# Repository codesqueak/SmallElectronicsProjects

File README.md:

# Small Electronics Projects

A collection of small projects for the Nascom 1 & 2 that don't need their own project space

# Nascom 1 Clock

A replacement, and somewhat less noisy, clock circuit

# Nascom 2 Graphics Adaptor

Full Nascom 2 graphics on the Nascom 1

# Nascom 2 Screen Flash Eliminator

A gadget to reduce screen flash on N2 video

# Solar Garden Light

Uses one NiMH battery and a 2.5v solar panel

# Grove to Raspberry Pi Adaptor

A simple adaptor to allow a set of Grove connector devices to be attached the to 5v/GND/SCL/SDA pins on the RPi connector

# Grove to Raspberry Pi Adaptor (Mixed)

A simple adaptor to allow a set of Grove connector devices to be attached the to 5v/GND/SCL/SDA pins on the RPi connector

# A LIPO Based Garden Light

Use a protected battery !

# A Compact  LIPO Based Garden Light

Use a protected battery !

# Nascom 1 Keyboard Adaptor

Small adaptor to allow use of the N2 keyboard connector on an N1

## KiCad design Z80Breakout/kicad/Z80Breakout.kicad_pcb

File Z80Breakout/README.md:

# Z80 Breakout Board

A board to allow easy access to Z80 pins / use of a ZIF socket

## Parts:

1. 40 pin ZIF socket
2. 2 x 20 turned pin SIL strips (Pins to go into the socket on the target system)
3. 2 x 20 pin SIL strip (Pins for the scope / LA connections). Lot’s on eBay – used a lot with RPi’s etc – Usually a lot cheaper than the turned pin strips !

## Construction

1. Solder the turned pin strips in first. (On the bottom of the board)
2. Trim down with snips on the top as the ZIF socket will sit on top of this.
3. Solder the scope / LA pin strips on the top of the board
4. Trim any pins sticking out the bottom
5. Solder in the ZIF socket – Be careful, it’s a bit close to the SIL strips used to insert into the CPU socket
6. Add pins to the +5v and GND via’s if you want these
7. Test all pins to make sure you have not shorted any while soldering.

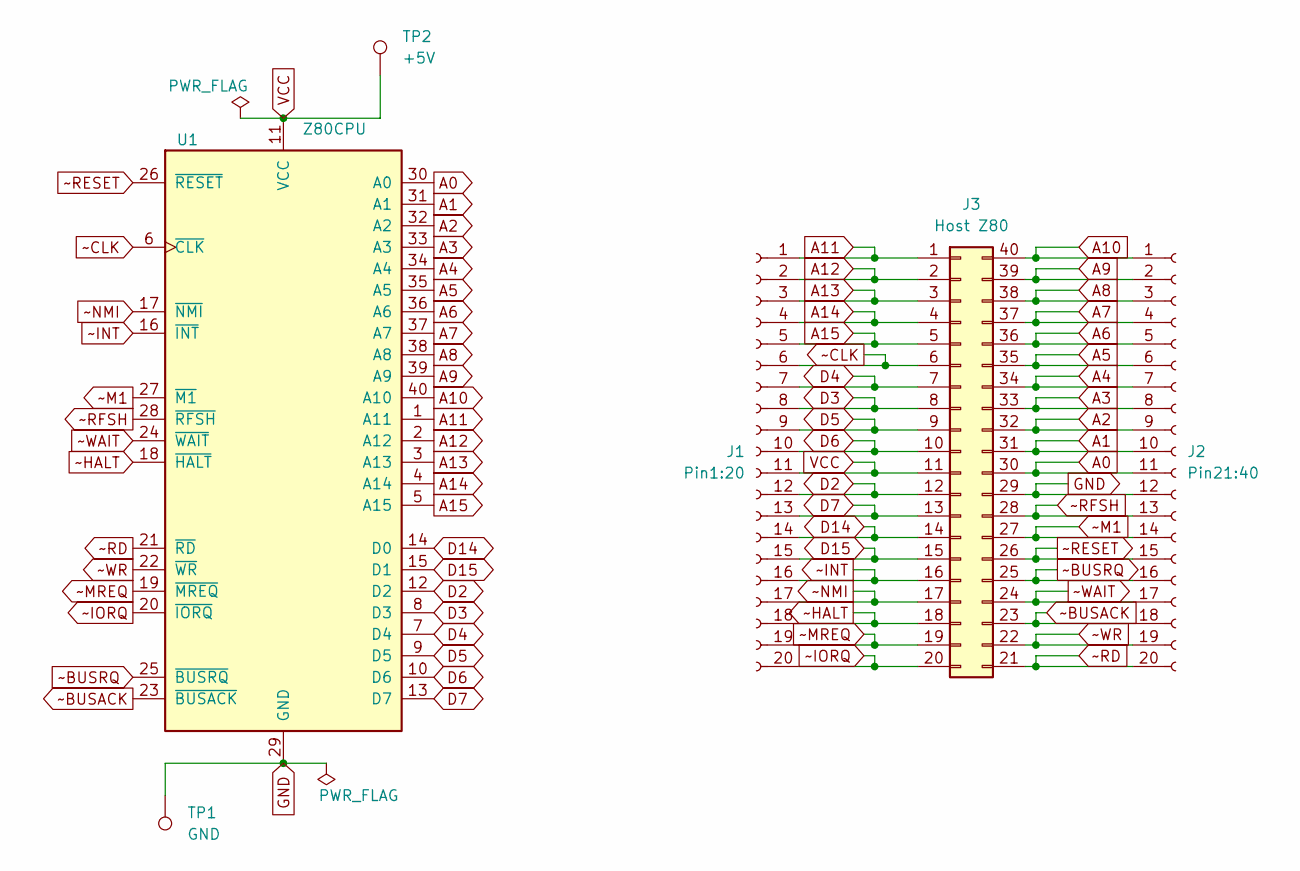
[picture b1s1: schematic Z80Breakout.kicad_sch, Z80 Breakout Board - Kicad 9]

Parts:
J1: Pin1:20; PinHeader_1x20_P2.54mm_Vertical
J2: Pin21:40; PinHeader_1x20_P2.54mm_Vertical
J3: Host Z80; DIP-40_W15.24mm
TP1: GND; TestPoint_THTPad_D2.0mm_Drill1.0mm
TP2: +5V; TestPoint_THTPad_D2.0mm_Drill1.0mm
U1: Z80CPU; DIP-40_W15.24mm_ZIF

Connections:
A0: J2.11, J3.30, U1.30 (A0)
A1: J2.10, J3.31, U1.31 (A1)
A2: J2.9, J3.32, U1.32 (A2)
A3: J2.8, J3.33, U1.33 (A3)
A4: J2.7, J3.34, U1.34 (A4)
A5: J2.6, J3.35, U1.35 (A5)
A6: J2.5, J3.36, U1.36 (A6)
A7: J2.4, J3.37, U1.37 (A7)
A8: J2.3, J3.38, U1.38 (A8)
A9: J2.2, J3.39, U1.39 (A9)
A10: J2.1, J3.40, U1.40 (A10)
A11: J1.1, J3.1, U1.1 (A11)
A12: J1.2, J3.2, U1.2 (A12)
A13: J1.3, J3.3, U1.3 (A13)
A14: J1.4, J3.4, U1.4 (A14)
A15: J1.5, J3.5, U1.5 (A15)
D2: J1.12, J3.12, U1.12 (D2)
D3: J1.8, J3.8, U1.8 (D3)
D4: J1.7, J3.7, U1.7 (D4)
D5: J1.9, J3.9, U1.9 (D5)
D6: J1.10, J3.10, U1.10 (D6)
D7: J1.13, J3.13, U1.13 (D7)
D14: J1.14, J3.14, U1.14 (D0)
D15: J1.15, J3.15, U1.15 (D1)
GND: J2.12, J3.29, TP1.1, U1.29 (GND)
VCC: J1.11, J3.11, TP2.1, U1.11 (VCC)
~BUSACK: J2.18, J3.23, U1.23 (~BUSACK)
~BUSRQ: J2.16, J3.25, U1.25 (~BUSRQ)
~CLK: J1.6, J3.6, U1.6 (~CLK)
~HALT: J1.18, J3.18, U1.18 (~HALT)
~INT: J1.16, J3.16, U1.16 (~INT)
~IORQ: J1.20, J3.20, U1.20 (~IORQ)
~M1: J2.14, J3.27, U1.27 (~M1)
~MREQ: J1.19, J3.19, U1.19 (~MREQ)
~NMI: J1.17, J3.17, U1.17 (~NMI)
~RD: J2.20, J3.21, U1.21 (~RD)
~RESET: J2.15, J3.26, U1.26 (~RESET)
~RFSH: J2.13, J3.28, U1.28 (~RFSH)
~WAIT: J2.17, J3.24, U1.24 (~WAIT)
~WR: J2.19, J3.22, U1.22 (~WR)

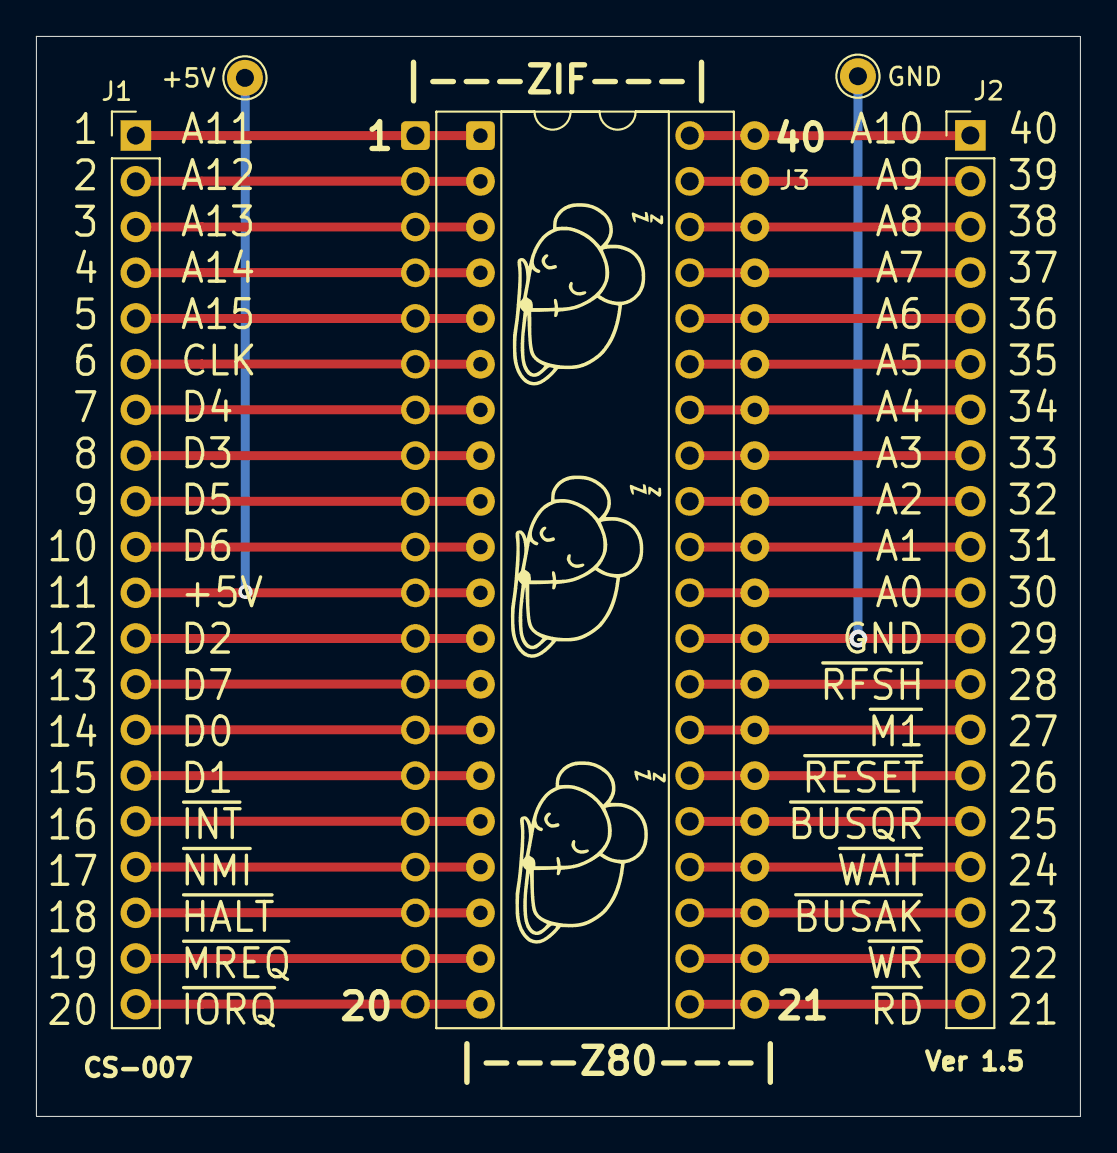
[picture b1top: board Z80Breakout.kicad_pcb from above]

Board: 2 copper layers, 58.0 x 60.0 mm, 9 parts (0 on the bottom side), 40 nets.

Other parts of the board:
G1, G1#2, G1#3: LOGO; sleepymouse_very_very_small

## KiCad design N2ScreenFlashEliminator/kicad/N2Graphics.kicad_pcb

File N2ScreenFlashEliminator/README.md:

# Nascom 2 Screen Flash Eliminator

A gadget to reduce screen flash on N2 video

## Introduction

This was developed from the long defunct add on from EDAC, as I found that the unclean video from the Nascom 2 lead to VGA converters having problems producing a stable image. This improved the output considerably in my experience.

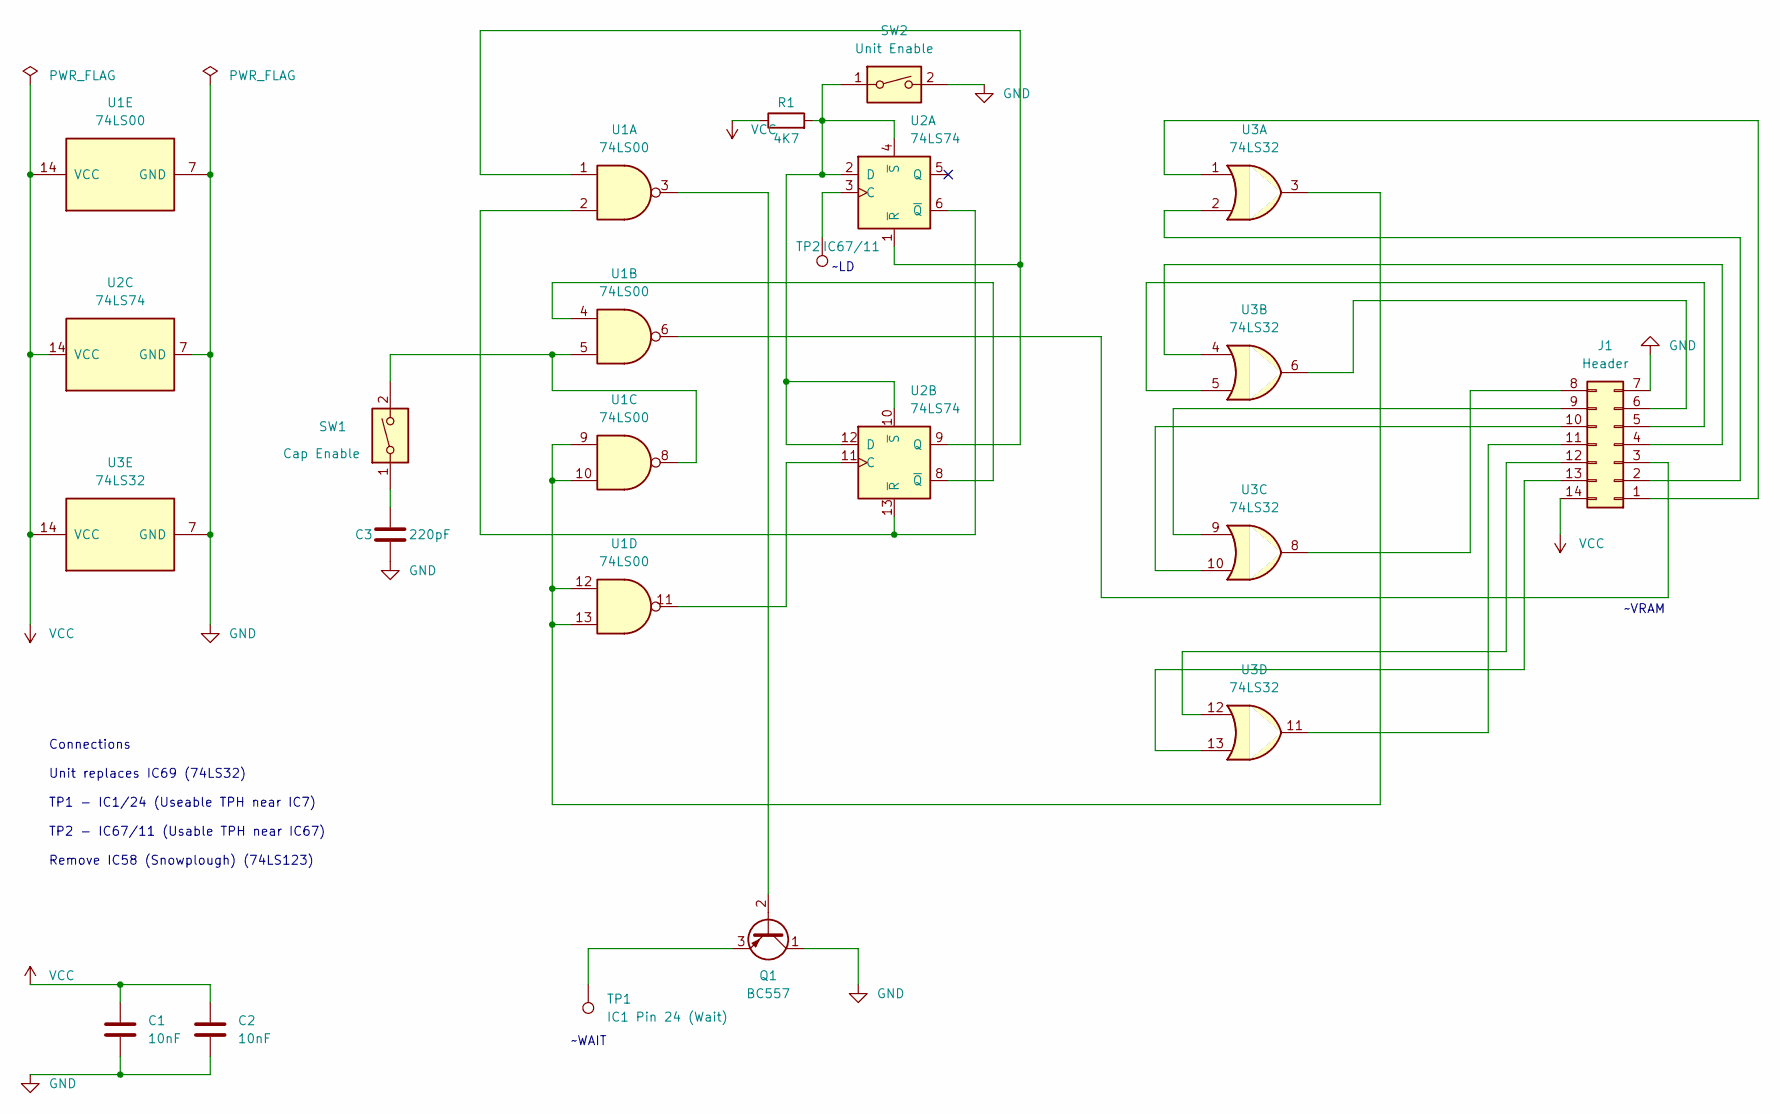
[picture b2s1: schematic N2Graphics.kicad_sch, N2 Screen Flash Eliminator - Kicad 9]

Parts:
C1, C2: 10nF; C_Disc_D3.4mm_W2.1mm_P2.50mm
C3: 220pF; C_Disc_D3.4mm_W2.1mm_P2.50mm
J1: Header; DIP-14_W7.62mm_Socket
Q1: BC557; TO-92_Inline_Wide
R1: 4K7; R_Axial_DIN0309_L9.0mm_D3.2mm_P12.70mm_Horizontal
SW1: Cap Enable; SW_DIP_SPSTx01_Slide_6.7x4.1mm_W7.62mm_P2.54mm_LowProfile
SW2: Unit Enable; SW_DIP_SPSTx01_Slide_6.7x4.1mm_W7.62mm_P2.54mm_LowProfile
TP1: IC1 Pin 24 (Wait); TestPoint_THTPad_D2.0mm_Drill1.0mm
TP2: IC67/11; TestPoint_THTPad_D2.0mm_Drill1.0mm
U1: 74LS00; DIP-14_W7.62mm_Socket
U2: 74LS74; DIP-14_W7.62mm_Socket
U3: 74LS32; DIP-14_W7.62mm_Socket

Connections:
GND: C1.2, C2.2, C3.2, J1.7, Q1.1 (C), SW2.2, U1.7 (GND), U2.7 (GND), U3.7 (GND)
unnamed: C3.1, SW1.1
unnamed: J1.1, U3.1
unnamed: J1.2, U3.2
unnamed: J1.3, U1.6
unnamed: J1.4, U3.4
unnamed: J1.5, U3.5
unnamed: J1.6, U3.6
unnamed: J1.8, U3.8
unnamed: J1.9, U3.9
unnamed: J1.10, U3.10
unnamed: J1.11, U3.11
unnamed: J1.12, U3.12
unnamed: J1.13, U3.13
unnamed: Q1.2 (B), U1.3
unnamed: Q1.3 (E), TP1.1
unnamed: SW1.2, U1.5, U1.8
unnamed: U1.9, U1.10, U1.12, U1.13, U3.3
unnamed: TP2.1, U2.3 (C)
unnamed: R1.2, SW2.1, U2.2 (D), U2.4 (~S), U2.10 (~S), U2.12 (D)
unnamed: U1.2, U2.6 (~Q), U2.13 (~R)
unnamed: U1.1, U2.1 (~R), U2.9 (Q)
unnamed: U1.11, U2.11 (C)
unnamed: U1.4, U2.8 (~Q)
VCC: C1.1, C2.1, J1.14, R1.1, U1.14 (VCC), U2.14 (VCC), U3.14 (VCC)

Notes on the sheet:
Connections Unit replaces IC69 (74LS32) TP1 - IC1/24 (Useable TPH near IC7) TP2 - IC67/11 (Usable TPH near IC67) Remove IC58 (Snowplough) (74LS123)
~VRAM
~WAIT
~LD

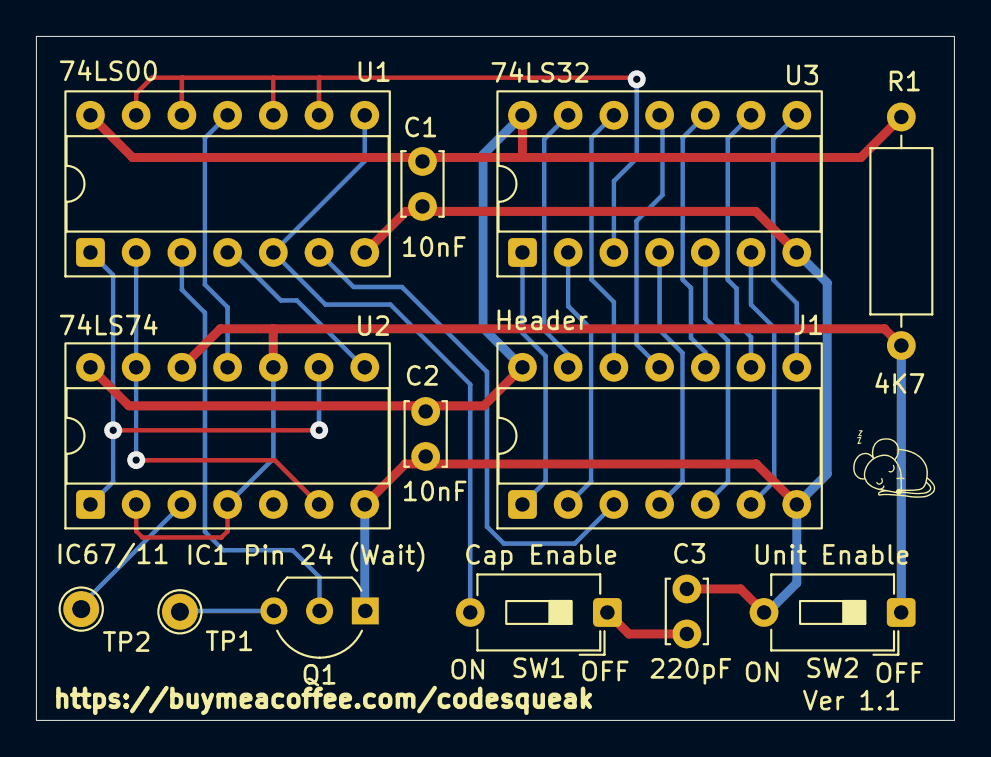
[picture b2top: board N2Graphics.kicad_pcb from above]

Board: 2 copper layers, 51.0 x 38.0 mm, 14 parts (0 on the bottom side), 25 nets.

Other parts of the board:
G1: LOGO; sleepymouse_tiny

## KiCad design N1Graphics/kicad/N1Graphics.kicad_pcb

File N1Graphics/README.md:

# Full Nascom 2 Graphics on a Nascom 1

This board allows full N2 graphics on a Nascom 1

## Introduction

This board accepts 2732 programmed with the complete Nascom 2 character set. This replaces  It replaces the existing Nascom 1 character ROM

Original data -> 0x0000 to 0x07FF

Graphics Data -> 0x0800 to 0x0FFF

Nascom 1 Required Modification

IC 20 Pin 12 to IC 17 Pin 18

IC 17 Pin 19 to IC 16 Pin 14

J1 wire link to IC 15 Pin 6 (Bend pin out of socket for wire link)

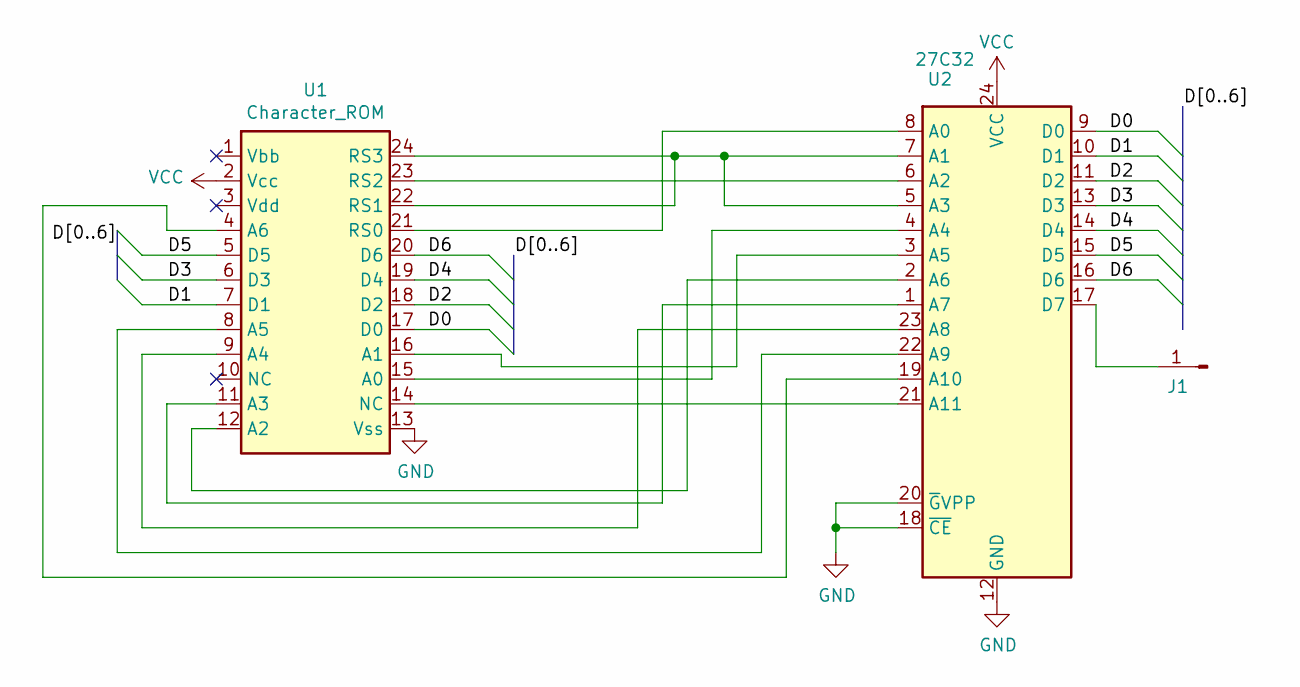
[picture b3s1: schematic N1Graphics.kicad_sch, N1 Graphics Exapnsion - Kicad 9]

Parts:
J1: Conn_01x01_Pin; PinHeader_1x01_P2.54mm_Vertical
U1: Character_ROM; DIP-24_W15.24mm
U2: 27C32; DIP-24_W15.24mm

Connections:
/D0: U1.17 (D0), U2.9 (D0)
/D1: U1.7 (D1), U2.10 (D1)
/D2: U1.18 (D2), U2.11 (D2)
/D3: U1.6 (D3), U2.13 (D3)
/D4: U1.19 (D4), U2.14 (D4)
/D5: U1.5 (D5), U2.15 (D5)
/D6: U1.20 (D6), U2.16 (D6)
GND: U1.13 (Vss), U2.12 (GND), U2.18 (~CE), U2.20 (~GVPP)
unnamed: J1.1, U2.17 (D7)
unnamed: U1.15 (A0), U2.4 (A4)
unnamed: U1.16 (A1), U2.3 (A5)
unnamed: U1.12 (A2), U2.2 (A6)
unnamed: U1.11 (A3), U2.1 (A7)
unnamed: U1.9 (A4), U2.23 (A8)
unnamed: U1.8 (A5), U2.22 (A9)
unnamed: U1.4 (A6), U2.19 (A10)
unnamed: U1.21 (RS0), U2.8 (A0)
unnamed: U1.22 (RS1), U1.24 (RS3), U2.5 (A3), U2.7 (A1)
unnamed: U1.23 (RS2), U2.6 (A2)
unnamed: U1.14 (NC), U2.21 (A11)
VCC: U1.2 (Vcc), U2.24 (VCC)

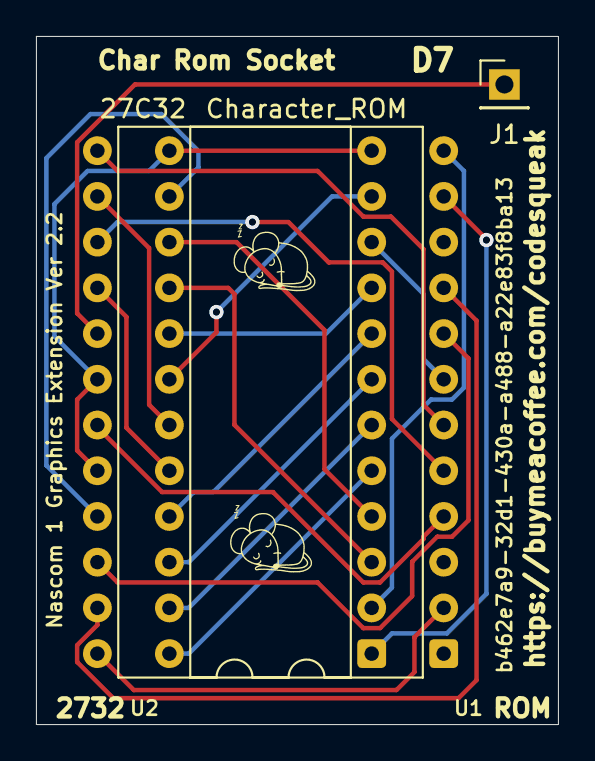
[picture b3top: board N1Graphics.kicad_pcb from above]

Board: 2 copper layers, 29.0 x 38.2 mm, 5 parts (0 on the bottom side), 21 nets.

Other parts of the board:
G001, G002: LOGO; sleepymouse_tiny

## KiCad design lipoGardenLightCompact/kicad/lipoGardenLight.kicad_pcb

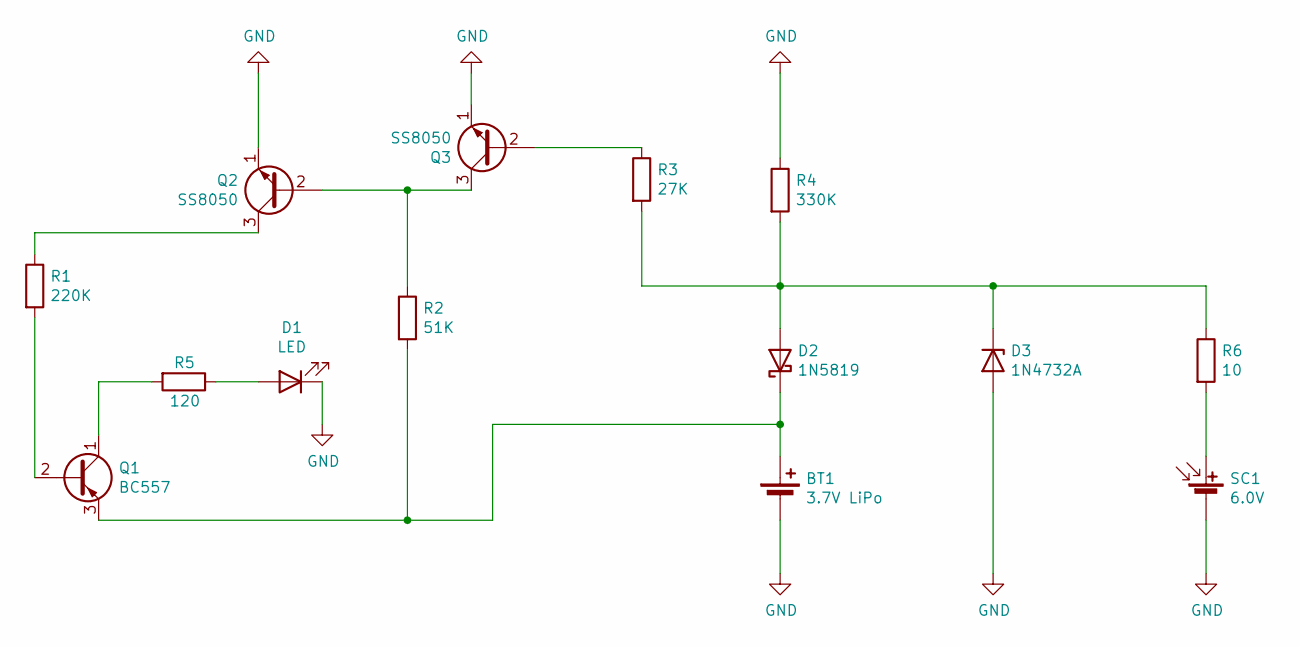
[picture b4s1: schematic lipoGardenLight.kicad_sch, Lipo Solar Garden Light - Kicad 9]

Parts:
BT1: 3.7V LiPo; JST_PH_B2B-PH-K_1x02_P2.00mm_Vertical
D1: LED; Wago_734-132_1x02_P3.50mm_Vertical
D2: 1N5819; D_DO-41_SOD81_P12.70mm_Horizontal
D3: 1N4732A; D_DO-41_SOD81_P12.70mm_Horizontal
Q1: BC557; TO-92_Inline_Wide
Q2, Q3: SS8050; TO-92_Inline_Wide
R1: 220K; R_Axial_DIN0309_L9.0mm_D3.2mm_P12.70mm_Horizontal
R2: 51K; R_Axial_DIN0309_L9.0mm_D3.2mm_P12.70mm_Horizontal
R3: 27K; R_Axial_DIN0309_L9.0mm_D3.2mm_P12.70mm_Horizontal
R4: 330K; R_Axial_DIN0309_L9.0mm_D3.2mm_P12.70mm_Horizontal
R5: 120; R_Axial_DIN0309_L9.0mm_D3.2mm_P12.70mm_Horizontal
R6: 10; R_Axial_DIN0309_L9.0mm_D3.2mm_P12.70mm_Horizontal
SC1: 6.0V; Wago_734-132_1x02_P3.50mm_Vertical

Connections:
GND: BT1.2 (-), D1.1 (K), D3.2 (A), Q2.1 (E), Q3.1 (E), R4.1, SC1.2 (-)
unnamed: BT1.1 (+), D2.1 (K), Q1.3 (E), R2.2
unnamed: D1.2 (A), R5.1
unnamed: D2.2 (A), D3.1 (K), R3.2, R4.2, R6.1
unnamed: Q1.2 (B), R1.2
unnamed: Q1.1 (C), R5.2
unnamed: Q2.2 (B), Q3.3 (C), R2.1
unnamed: Q2.3 (C), R1.1
unnamed: Q3.2 (B), R3.1
unnamed: R6.2, SC1.1 (+)

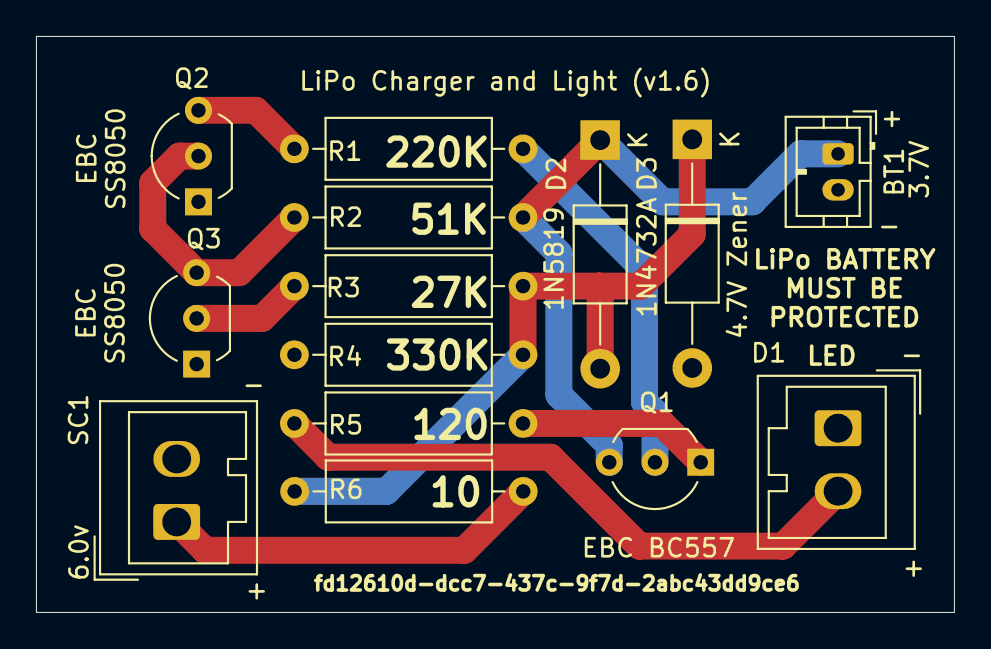
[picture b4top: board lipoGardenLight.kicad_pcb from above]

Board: 2 copper layers, 51.0 x 32.0 mm, 14 parts (0 on the bottom side), 10 nets.

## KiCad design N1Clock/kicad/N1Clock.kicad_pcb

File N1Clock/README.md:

# Better Nascom 1 Clock

The original clock is awful !

## Introduction

...

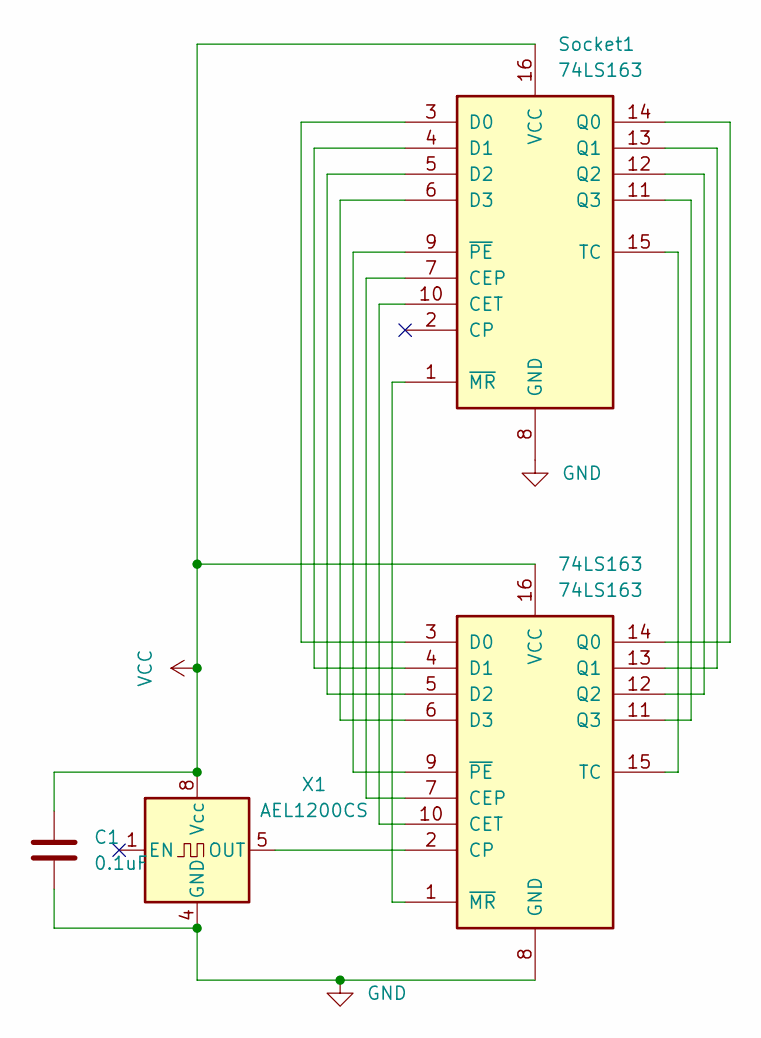
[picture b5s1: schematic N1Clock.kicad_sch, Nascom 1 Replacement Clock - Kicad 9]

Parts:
74LS163: 74LS163; DIP-16_W7.62mm
C1: 0.1uF; C_Disc_D5.0mm_W2.5mm_P5.00mm
Socket1: 74LS163; DIP-16_W7.62mm_Socket
X1: AEL1200CS; Oscillator_DIP-8

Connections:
GND: 74LS163.8 (GND), C1.2, Socket1.8 (GND), X1.4 (GND)
unnamed: 74LS163.7 (CEP), Socket1.7 (CEP)
unnamed: 74LS163.10 (CET), Socket1.10 (CET)
unnamed: 74LS163.2 (CP), X1.5 (OUT)
unnamed: 74LS163.3 (D0), Socket1.3 (D0)
unnamed: 74LS163.4 (D1), Socket1.4 (D1)
unnamed: 74LS163.5 (D2), Socket1.5 (D2)
unnamed: 74LS163.6 (D3), Socket1.6 (D3)
unnamed: 74LS163.14 (Q0), Socket1.14 (Q0)
unnamed: 74LS163.13 (Q1), Socket1.13 (Q1)
unnamed: 74LS163.12 (Q2), Socket1.12 (Q2)
unnamed: 74LS163.11 (Q3), Socket1.11 (Q3)
unnamed: 74LS163.15 (TC), Socket1.15 (TC)
unnamed: 74LS163.1 (~MR), Socket1.1 (~MR)
unnamed: 74LS163.9 (~PE), Socket1.9 (~PE)
VCC: 74LS163.16 (VCC), C1.1, Socket1.16 (VCC), X1.8 (Vcc)

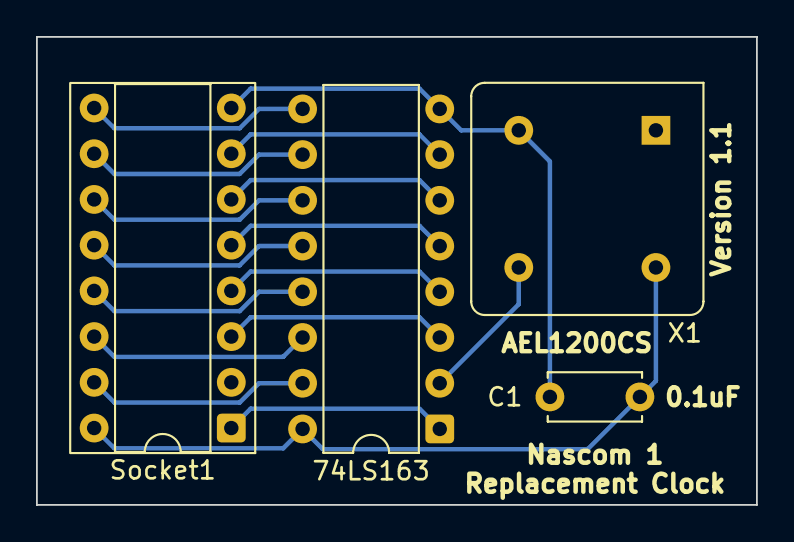
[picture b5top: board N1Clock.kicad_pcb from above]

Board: 2 copper layers, 40.0 x 26.0 mm, 4 parts (0 on the bottom side), 16 nets.

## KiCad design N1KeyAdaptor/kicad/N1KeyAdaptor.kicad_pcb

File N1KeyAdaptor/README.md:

# Nascom 1 Keyboard Adaptor

Small adaptor to allow use of the N2 keyboard connector on an N1

## Introduction

...

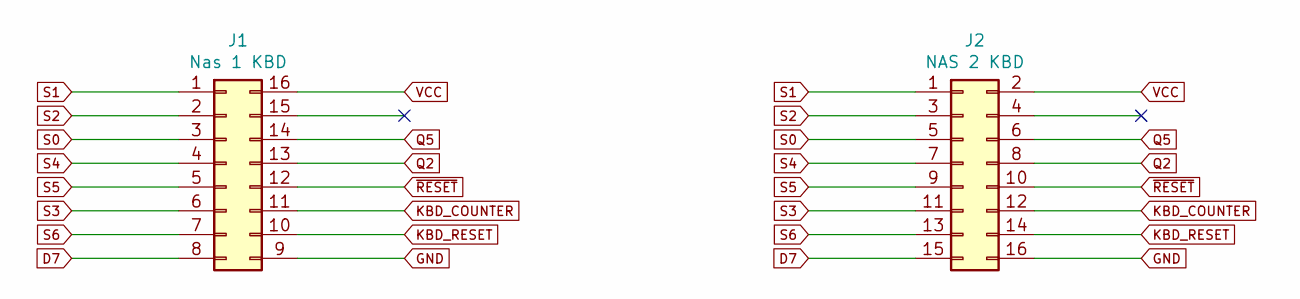
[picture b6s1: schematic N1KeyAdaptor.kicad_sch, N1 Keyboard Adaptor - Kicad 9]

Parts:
J1: Nas 1 KBD; DIP-16_W7.62mm_Socket
J2: NAS 2 KBD; PinHeader_2x08_P2.54mm_Vertical

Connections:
D7: J1.8, J2.15
GND: J1.9, J2.16
KBD_COUNTER: J1.11, J2.12
KBD_RESET: J1.10, J2.14
Q2: J1.13, J2.8
Q5: J1.14, J2.6
S0: J1.3, J2.5
S1: J1.1, J2.1
S2: J1.2, J2.3
S3: J1.6, J2.11
S4: J1.4, J2.7
S5: J1.5, J2.9
S6: J1.7, J2.13
VCC: J1.16, J2.2
~RESET: J1.12, J2.10

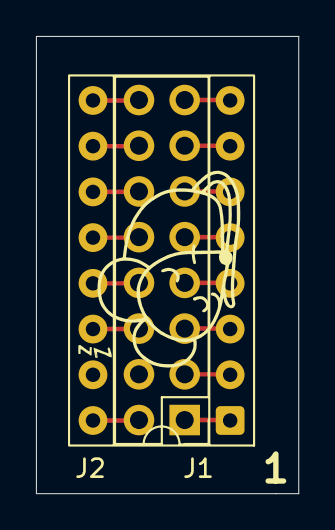
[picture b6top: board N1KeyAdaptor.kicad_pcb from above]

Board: 2 copper layers, 14.6 x 25.4 mm, 3 parts (0 on the bottom side), 15 nets.

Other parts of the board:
G001: LOGO

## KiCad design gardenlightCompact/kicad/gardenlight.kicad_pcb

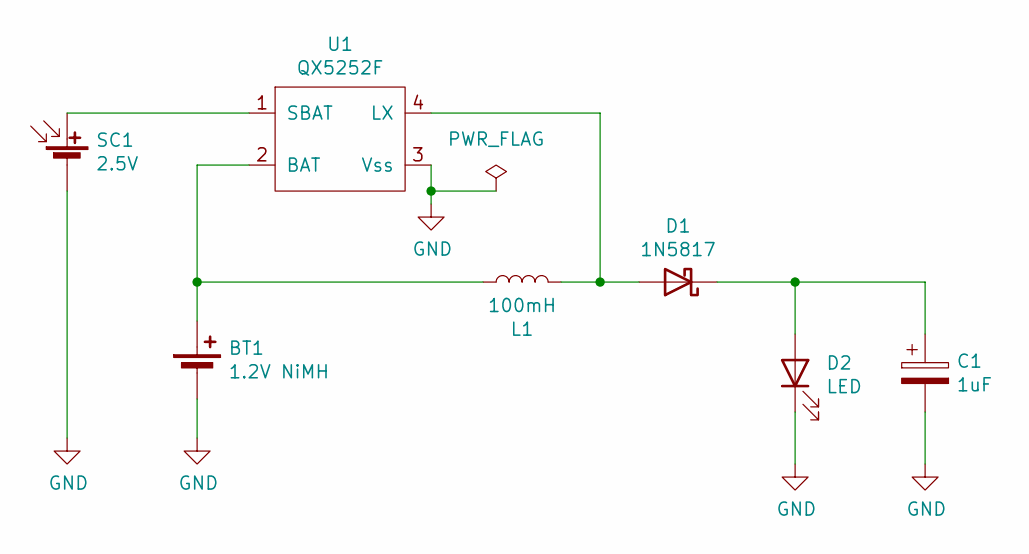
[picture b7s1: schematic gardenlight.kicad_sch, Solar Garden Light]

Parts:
BT1: 1.2V NiMH; JST_PH_B2B-PH-K_1x02_P2.00mm_Vertical
C1: 1uF; CP_Radial_D4.0mm_P1.50mm
D1: 1N5817; D_DO-41_SOD81_P10.16mm_Horizontal
D2: LED; LED_D5.0mm
L1: 100mH; L_Axial_L6.6mm_D2.7mm_P10.16mm_Horizontal_Vishay_IM-2
SC1: 2.5V; JST_PH_B2B-PH-K_1x02_P2.00mm_Vertical
U1: QX5252F

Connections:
GND: BT1.2 (-), C1.2, D2.1 (K), SC1.2 (-), U1.3 (Vss)
unnamed: BT1.1 (+), L1.1, U1.2 (BAT)
unnamed: D1.2 (A), L1.2, U1.4 (LX)
unnamed: C1.1, D1.1 (K), D2.2 (A)
unnamed: SC1.1 (+), U1.1 (SBAT)

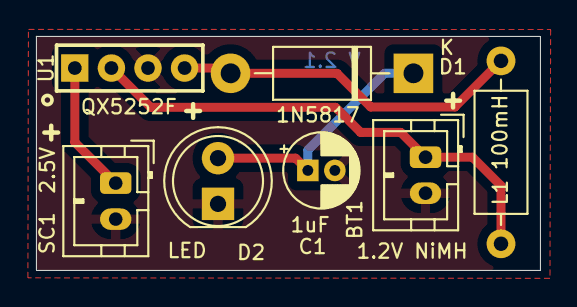
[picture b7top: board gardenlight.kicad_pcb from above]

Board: 2 copper layers, 28.0 x 13.0 mm, 7 parts (0 on the bottom side), 5 nets.

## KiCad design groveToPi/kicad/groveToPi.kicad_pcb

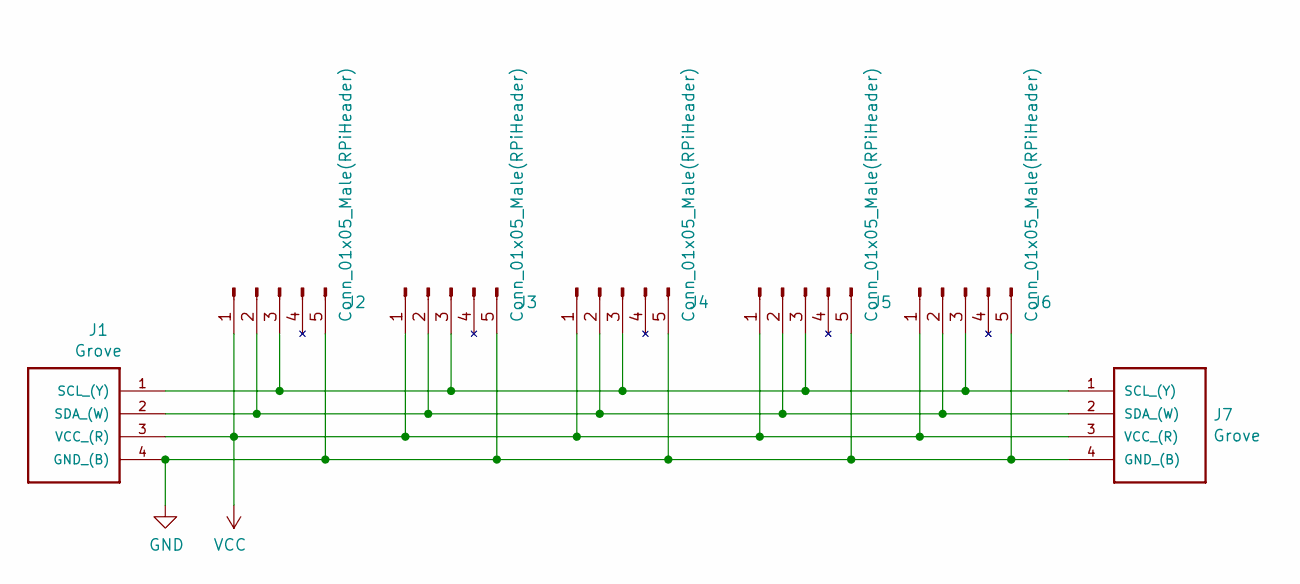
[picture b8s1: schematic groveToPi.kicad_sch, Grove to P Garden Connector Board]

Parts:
J1, J7: Grove; GroveConnector
J2, J3, J4, J5, J6: Conn_01x05_Male(RPiHeader); PinSocket_1x05_P2.54mm_Vertical

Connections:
GND: J1.4 (GND_(B)), J2.5, J3.5, J4.5, J5.5, J6.5, J7.4 (GND_(B))
unnamed: J1.1 (SCL_(Y)), J2.3, J3.3, J4.3, J5.3, J6.3, J7.1 (SCL_(Y))
unnamed: J1.2 (SDA_(W)), J2.2, J3.2, J4.2, J5.2, J6.2, J7.2 (SDA_(W))
VCC: J1.3 (VCC_(R)), J2.1, J3.1, J4.1, J5.1, J6.1, J7.3 (VCC_(R))

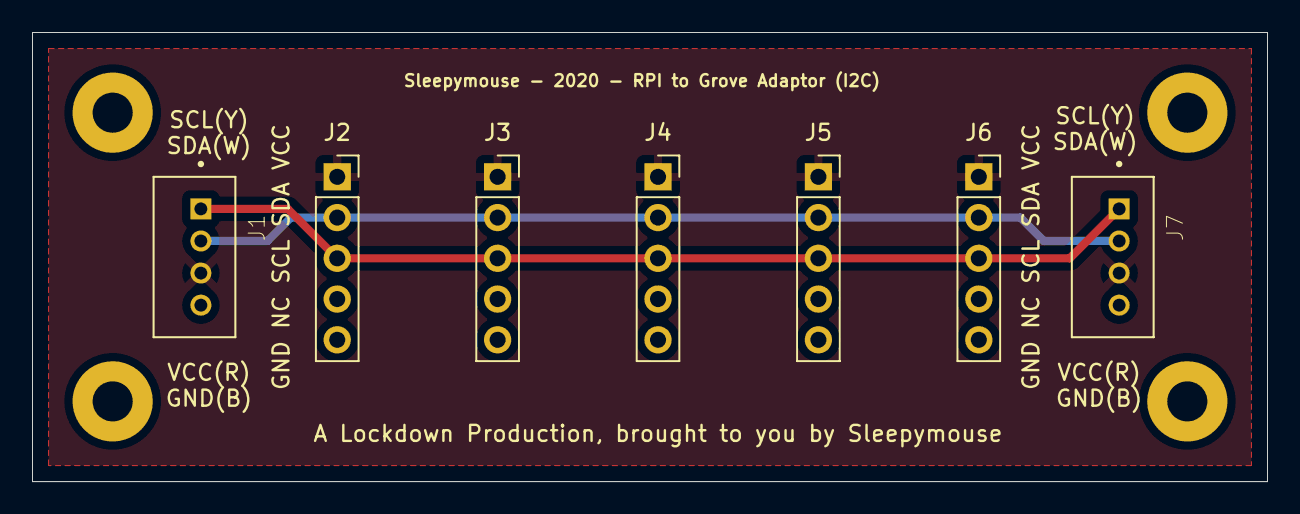
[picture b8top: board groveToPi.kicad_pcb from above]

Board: 2 copper layers, 77.0 x 28.0 mm, 7 parts (0 on the bottom side), 4 nets.

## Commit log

2023-12-06 Initial upload
2024-01-14 LiPo Solar Garden Light
2024-01-14 Small Garden Light
2024-01-14 Remove gerbers
2024-01-14 tidy up
2024-02-17 Various small projects
2024-02-17 Tweak README
2024-03-03 Flip enable switch position
2024-03-03 Update pics
2024-03-12 Update PCB's
2024-03-17 Docs
2024-04-09 Add Z80 breakout board
2024-04-21 Z80 Breakout
2024-07-21 Add photo
2024-10-30 Kicad 8 / minor tweaks
2024-10-30 Readme update
2024-11-30 Updaate breakout docs
2025-04-26 Kicad 9 updates
2025-05-04 Minor changes
